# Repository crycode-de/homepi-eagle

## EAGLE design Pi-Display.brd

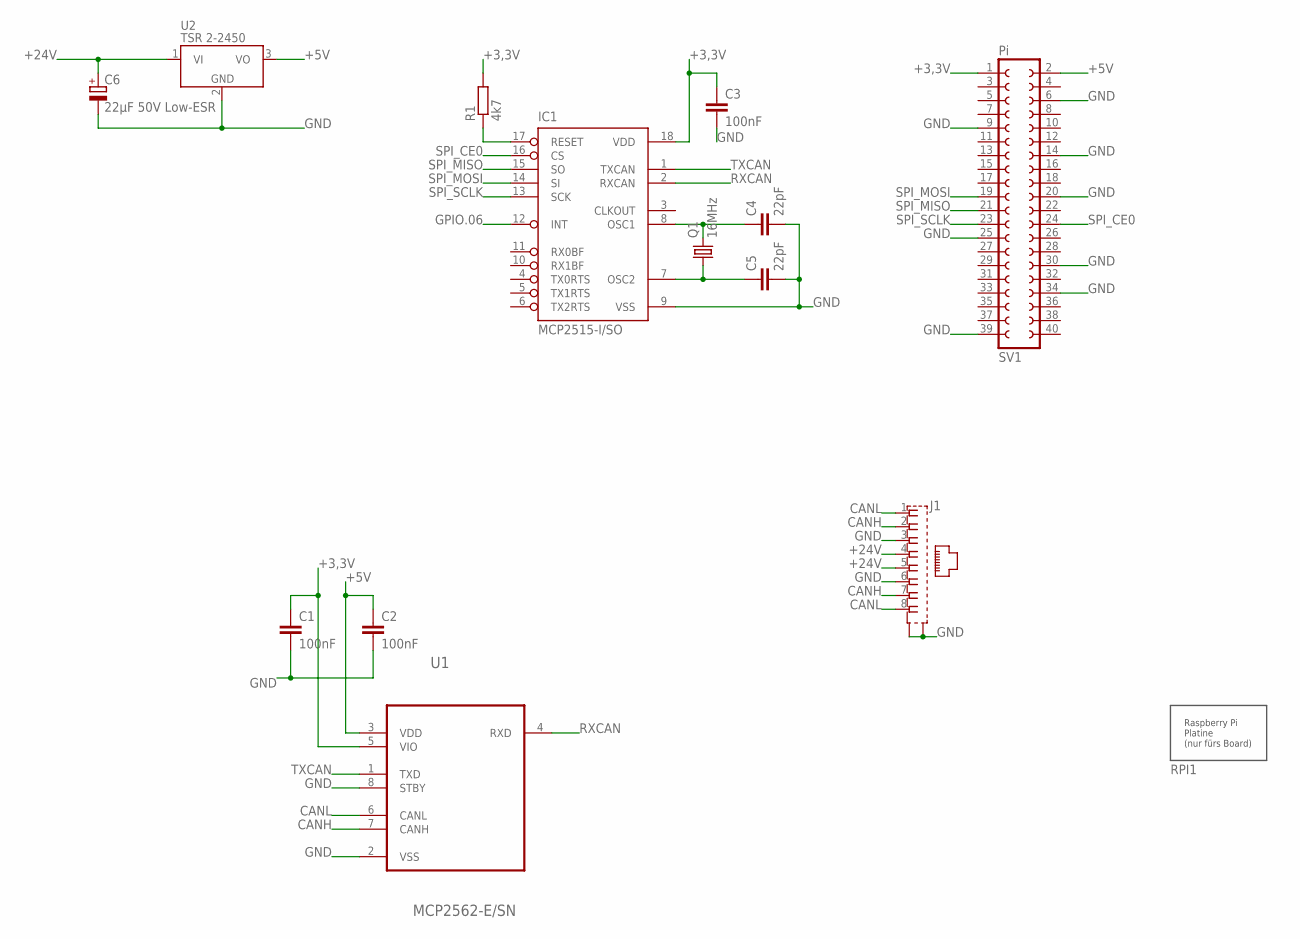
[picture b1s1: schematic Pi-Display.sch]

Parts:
C1, C2, C3: 100nF; C1206
C4, C5: 22pF; C1206
C6: 22µF 50V Low-ESR; E2-5
IC1: MCP2515-I/SO; SO18L
J1: 555141-1; MEBP_8-8G
Q1: 16MHz; HC49UP
R1: 4k7; R1206
RPI1: RASPBERRYPI-PLATINE
SV1: Pi; FE20-2
U1: MCP2562-E/SN; SO08
U2: TSR 2-2450; TSR-1

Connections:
+3,3V: C1.1, C3.1, IC1.18 (VDD), R1.2, SV1.1, U1.5 (VIO)
+5V: C2.1, SV1.2, U1.3 (VDD), U2.3 (VO)
+24V: C6.+, J1.4, J1.5, U2.1 (VI)
CANH: J1.2, J1.7, U1.7 (CANH)
CANL: J1.1, J1.8, U1.6 (CANL)
GND: C1.2, C2.2, C3.2, C4.2, C5.2, C6.-, IC1.9 (VSS), J1.3, J1.6, J1.G1 (S1), J1.G2 (S2), SV1.6, SV1.9, SV1.14, SV1.20, SV1.25, SV1.30, SV1.34, SV1.39, U1.2 (VSS), U1.8 (STBY), U2.2 (GND)
GPIO.06: IC1.12 (INT)
unnamed: C4.1, IC1.8 (OSC1), Q1.2
unnamed: IC1.17 (RESET), R1.1
unnamed: C5.1, IC1.7 (OSC2), Q1.1
RXCAN: IC1.2 (RXCAN), U1.4 (RXD)
SPI_CE0: IC1.16 (CS), SV1.24
SPI_MISO: IC1.15 (SO), SV1.21
SPI_MOSI: IC1.14 (SI), SV1.19
SPI_SCLK: IC1.13 (SCK), SV1.23
TXCAN: IC1.1 (TXCAN), U1.1 (TXD)

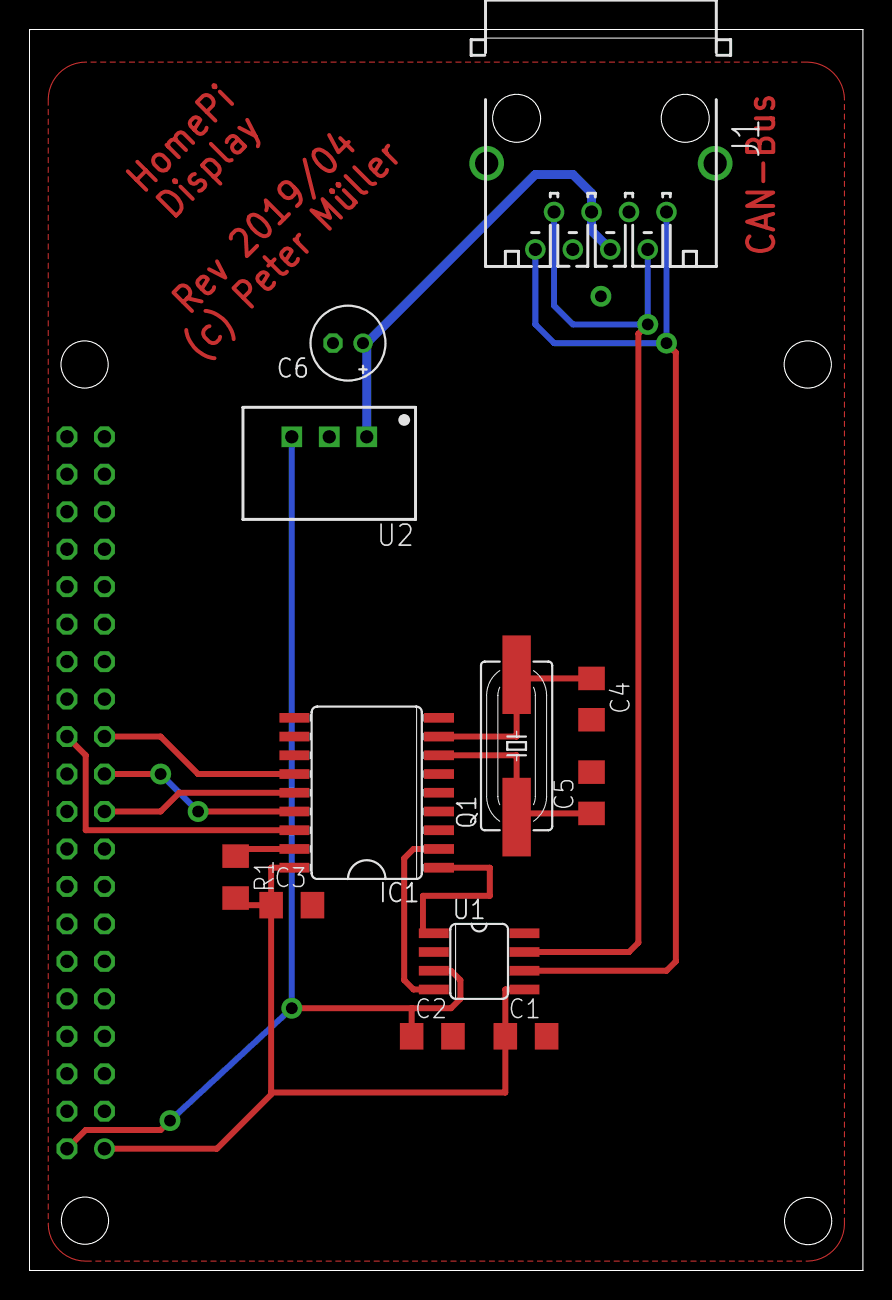
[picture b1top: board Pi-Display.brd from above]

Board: 2 copper layers, 56.5 x 84.1 mm, 14 parts (1 on the bottom side), 15 nets.

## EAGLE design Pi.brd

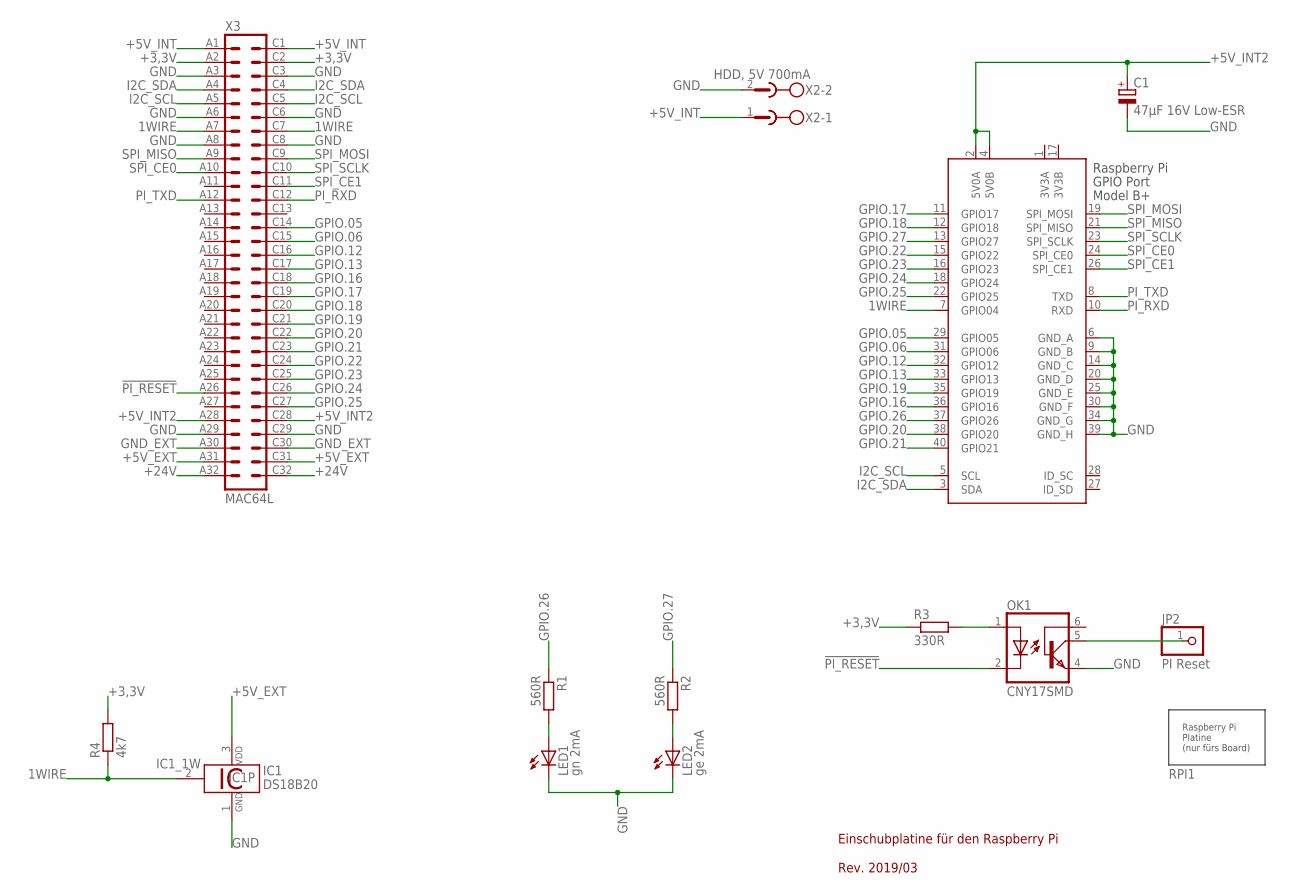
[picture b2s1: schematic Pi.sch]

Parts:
C1: 47µF 16V Low-ESR; E2-5
IC1: DS18B20; TO92-
JP2: PI Reset; 1X01
LED1: gn 2mA; LED3MM
LED2: ge 2mA; LED3MM
OK1: CNY17SMD; DIL06_SMD
R1, R2: 560R; R1206
R3: 330R; R1206
R4: 4k7; R1206
RPI1: RASPBERRYPI-PLATINE
X1: RASPI_GPIO_B+#_PIN; RASPI_GPIO_B+_PIN
X2: HDD, 5V 700mA; MSTBV2
X3: MAC64L

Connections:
1WIRE: IC1.2 (1W), R4.1, X1.7 (GPIO04), X3.A7, X3.C7
3V3A: X1.1 (3V3A)
3V3B: X1.17 (3V3B)
!PI_RESET: OK1.2 (C), X3.A26
+3,3V: R3.1, R4.2, X3.A2, X3.C2
+5V_EXT: IC1.3 (VDD), X3.A31, X3.C31
+5V_INT: X2.1, X3.A1, X3.C1
+5V_INT2: C1.+, X1.2 (5V0A), X1.4 (5V0B), X3.A28, X3.C28
+24V: X3.A32, X3.C32
GND: C1.-, IC1.1 (GND), LED1.K (C), LED2.K (C), OK1.4 (EMI), X1.6 (GND_A), X1.9 (GND_B), X1.14 (GND_C), X1.20 (GND_D), X1.25 (GND_E), X1.30 (GND_F), X1.34 (GND_G), X1.39 (GND_H), X2.2, X3.A3, X3.A6, X3.A8, X3.A29, X3.C3, X3.C6, X3.C8, X3.C29
GND_EXT: X3.A30, X3.C30
GPIO.05: X1.29 (GPIO05), X3.C14
GPIO.06: X1.31 (GPIO06), X3.C15
GPIO.12: X1.32 (GPIO12), X3.C16
GPIO.13: X1.33 (GPIO13), X3.C17
GPIO.16: X1.36 (GPIO16), X3.C18
GPIO.17: X1.11 (GPIO17), X3.C19
GPIO.18: X1.12 (GPIO18), X3.C20
GPIO.19: X1.35 (GPIO19), X3.C21
GPIO.20: X1.38 (GPIO20), X3.C22
GPIO.21: X1.40 (GPIO21), X3.C23
GPIO.22: X1.15 (GPIO22), X3.C24
GPIO.23: X1.16 (GPIO23), X3.C25
GPIO.24: X1.18 (GPIO24), X3.C26
GPIO.25: X1.22 (GPIO25), X3.C27
GPIO.26: R1.1, X1.37 (GPIO26)
GPIO.27: R2.1, X1.13 (GPIO27)
I2C_SCL: X1.5 (SCL), X3.A5, X3.C5
I2C_SDA: X1.3 (SDA), X3.A4, X3.C4
unnamed: LED2.A, R2.2
unnamed: OK1.1 (A), R3.2
unnamed: JP2.1, OK1.5 (COL)
unnamed: LED1.A, R1.2
PI_RXD: X1.10 (RXD), X3.C12
PI_TXD: X1.8 (TXD), X3.A12
SPI_CE0: X1.24 (SPI_CE0), X3.A10
SPI_CE1: X1.26 (SPI_CE1), X3.C11
SPI_MISO: X1.21 (SPI_MISO), X3.A9
SPI_MOSI: X1.19 (SPI_MOSI), X3.C9
SPI_SCLK: X1.23 (SPI_SCLK), X3.C10

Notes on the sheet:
Einschubplatine für den Raspberry Pi Rev. 2019/03

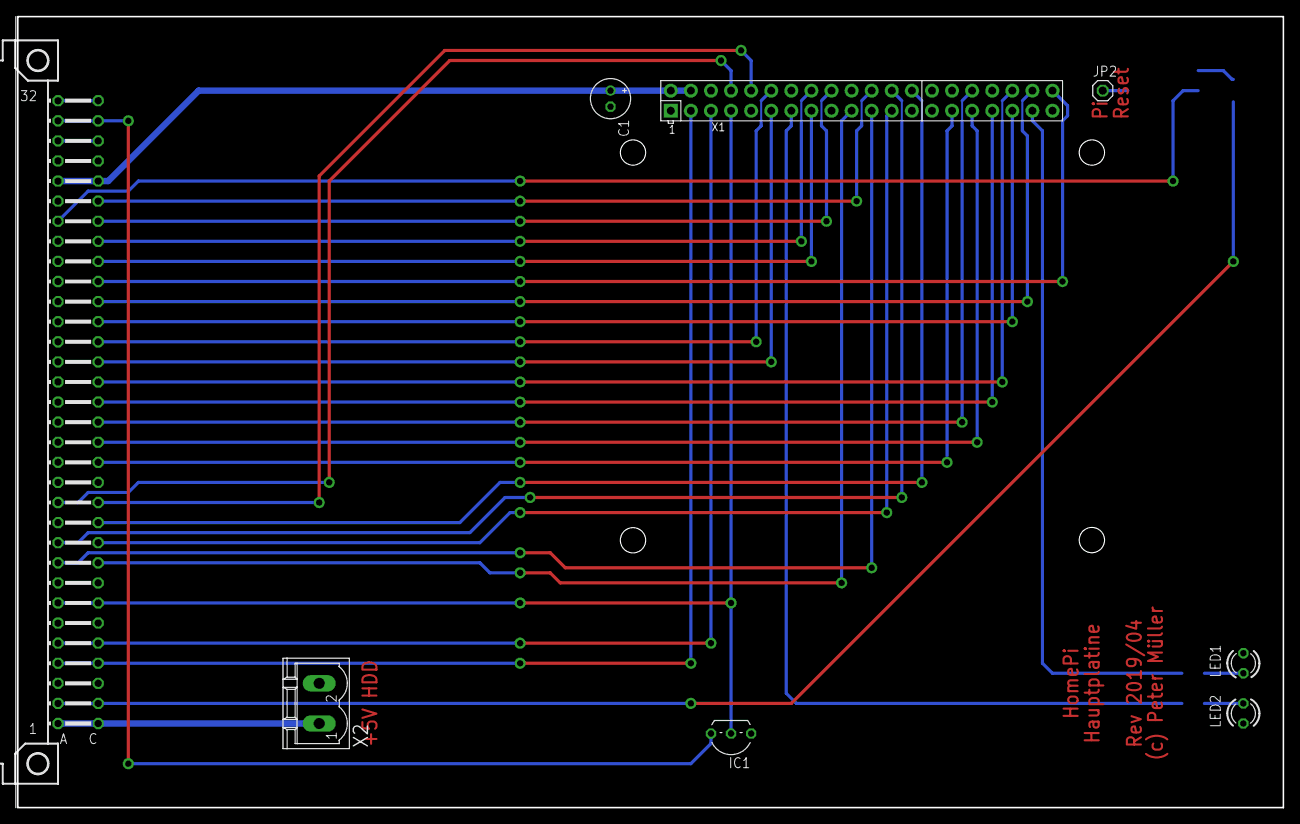
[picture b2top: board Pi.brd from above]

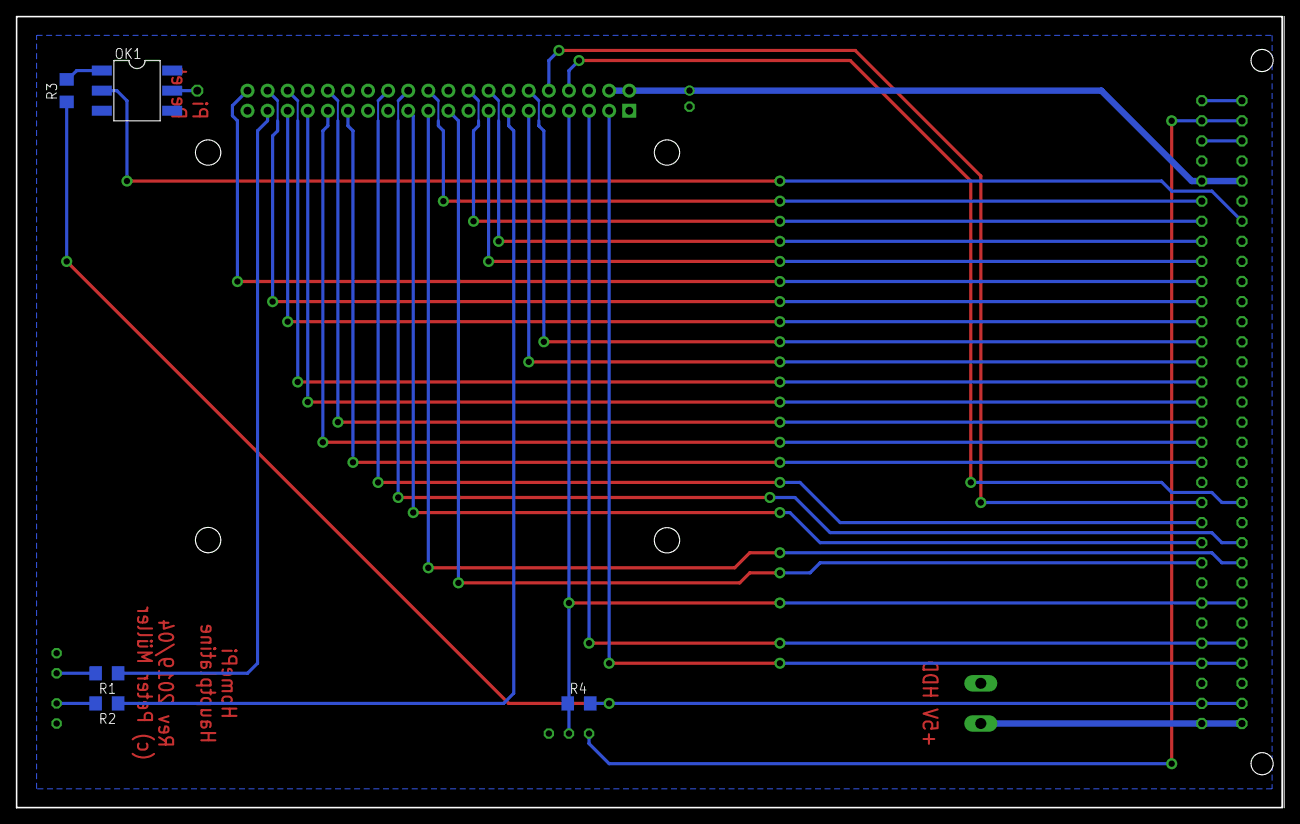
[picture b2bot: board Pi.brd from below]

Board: 2 copper layers, 160.0 x 100.0 mm, 14 parts (5 on the bottom side), 38 nets.

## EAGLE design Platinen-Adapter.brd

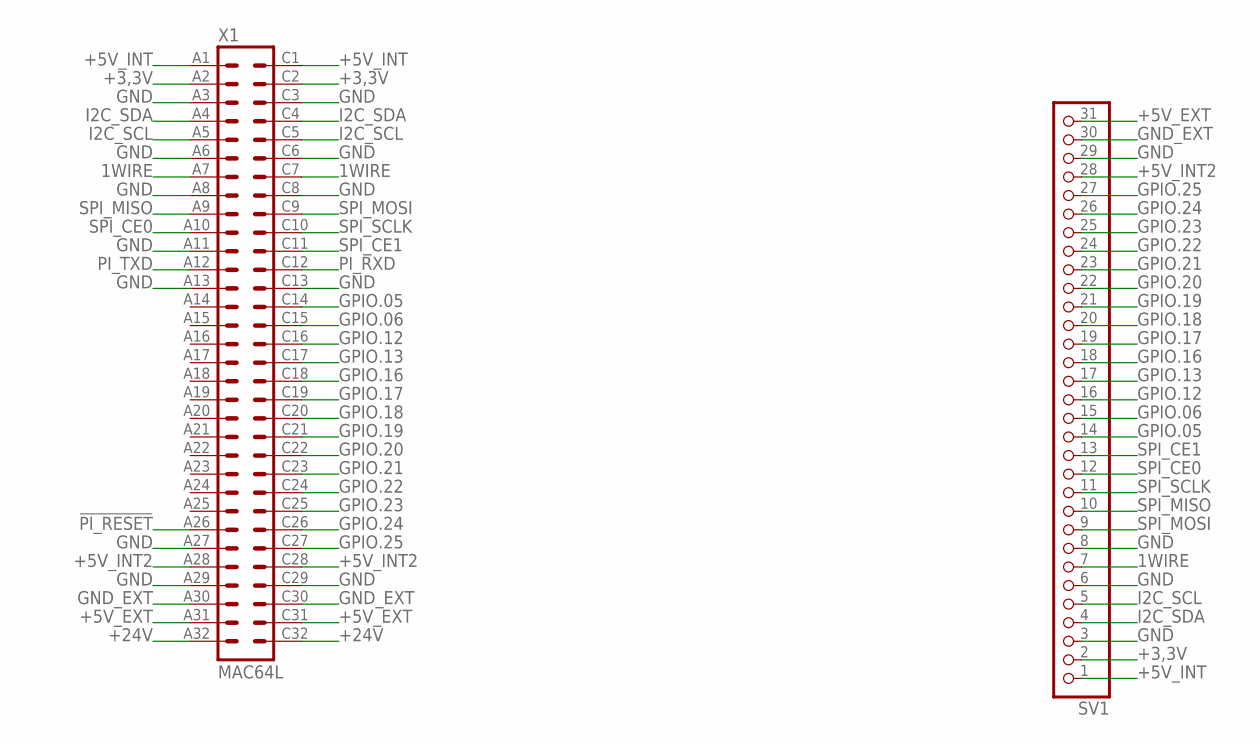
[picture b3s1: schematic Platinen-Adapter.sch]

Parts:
SV1: PINHD-1X31; 1X31
X1: MAC64L

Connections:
1WIRE: SV1.7, X1.A7, X1.C7
!PI_RESET: X1.A26
+3,3V: SV1.2, X1.A2, X1.C2
+5V_EXT: SV1.31, X1.A31, X1.C31
+5V_INT: SV1.1, X1.A1, X1.C1
+5V_INT2: SV1.28, X1.A28, X1.C28
+24V: X1.A32, X1.C32
GND: SV1.3, SV1.6, SV1.8, SV1.29, X1.A3, X1.A6, X1.A8, X1.A11, X1.A13, X1.A27, X1.A29, X1.C3, X1.C6, X1.C8, X1.C13, X1.C29
GND_EXT: SV1.30, X1.A30, X1.C30
GPIO.05: SV1.14, X1.C14
GPIO.06: SV1.15, X1.C15
GPIO.12: SV1.16, X1.C16
GPIO.13: SV1.17, X1.C17
GPIO.16: SV1.18, X1.C18
GPIO.17: SV1.19, X1.C19
GPIO.18: SV1.20, X1.C20
GPIO.19: SV1.21, X1.C21
GPIO.20: SV1.22, X1.C22
GPIO.21: SV1.23, X1.C23
GPIO.22: SV1.24, X1.C24
GPIO.23: SV1.25, X1.C25
GPIO.24: SV1.26, X1.C26
GPIO.25: SV1.27, X1.C27
I2C_SCL: SV1.5, X1.A5, X1.C5
I2C_SDA: SV1.4, X1.A4, X1.C4
PI_RXD: X1.C12
PI_TXD: X1.A12
SPI_CE0: SV1.12, X1.A10
SPI_CE1: SV1.13, X1.C11
SPI_MISO: SV1.10, X1.A9
SPI_MOSI: SV1.9, X1.C9
SPI_SCLK: SV1.11, X1.C10

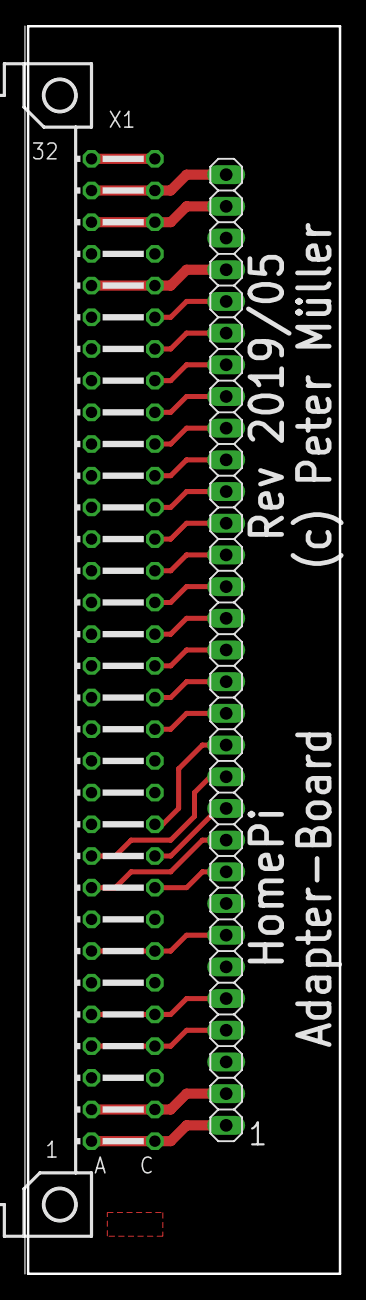
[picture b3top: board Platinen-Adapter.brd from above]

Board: 2 copper layers, 25.0 x 100.0 mm, 3 parts (1 on the bottom side), 29 nets.

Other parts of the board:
U$2: 30MM

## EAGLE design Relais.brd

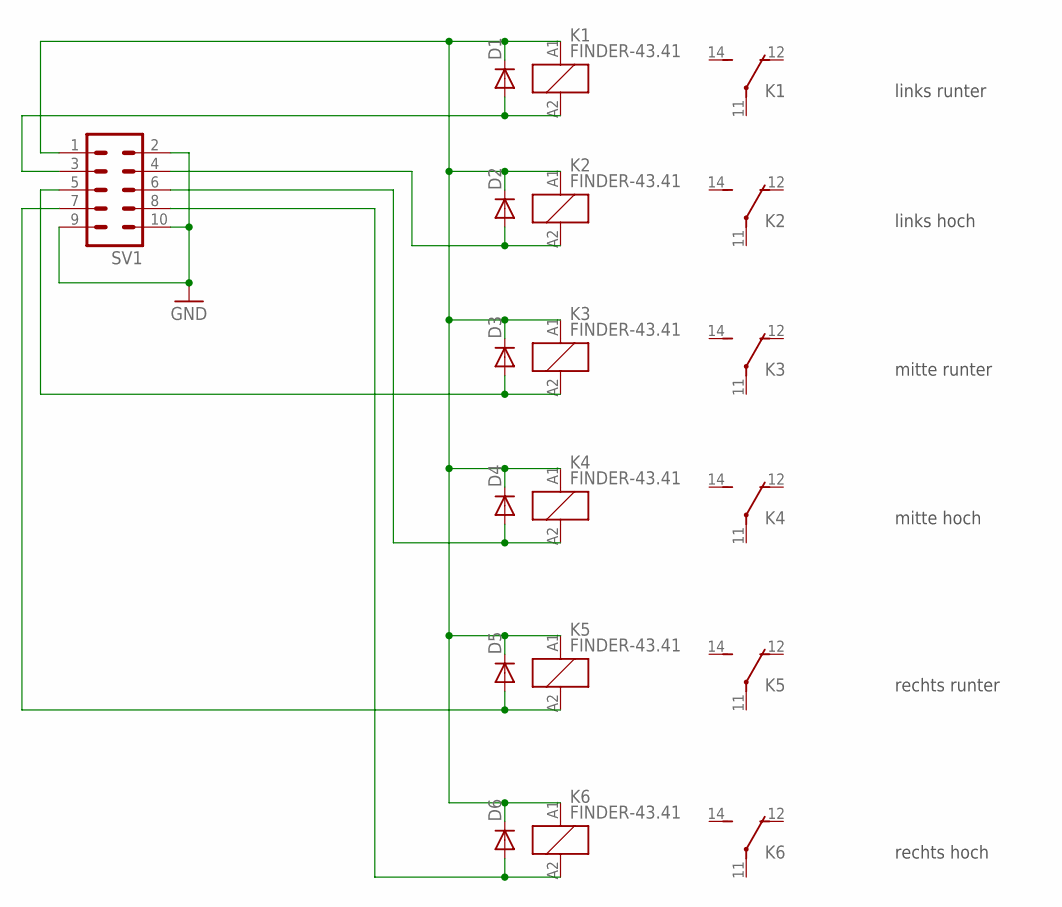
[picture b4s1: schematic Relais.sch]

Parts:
D1, D2, D3, D4, D5, D6: DIODE-D-7.5; D-7.5
K1, K2, K3, K4, K5, K6: FINDER-43.41
SV1: ML10

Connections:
GND: SV1.2, SV1.9, SV1.10
unnamed: D1.A, K1.A2 (2), SV1.3
unnamed: D2.A, K2.A2 (2), SV1.4
unnamed: D3.A, K3.A2 (2), SV1.5
unnamed: D4.A, K4.A2 (2), SV1.6
unnamed: D5.A, K5.A2 (2), SV1.7
unnamed: D6.A, K6.A2 (2), SV1.8
VCC: D1.C, D2.C, D3.C, D4.C, D5.C, D6.C, K1.A1 (1), K2.A1 (1), K3.A1 (1), K4.A1 (1), K5.A1 (1), K6.A1 (1), SV1.1

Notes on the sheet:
links runter
links hoch
mitte runter
mitte hoch
rechts runter
rechts hoch

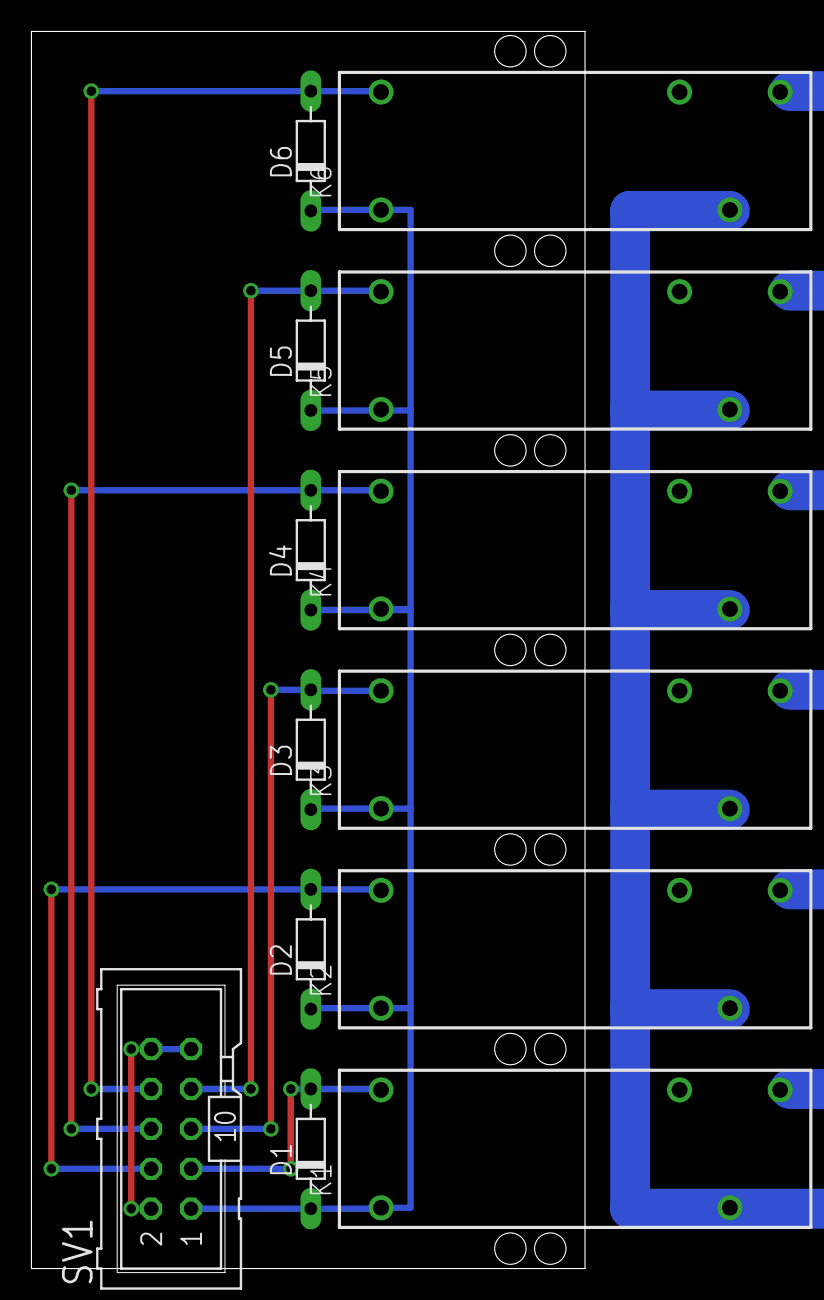
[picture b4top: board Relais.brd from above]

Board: 2 copper layers, 35.2 x 78.7 mm, 13 parts (0 on the bottom side), 8 nets.

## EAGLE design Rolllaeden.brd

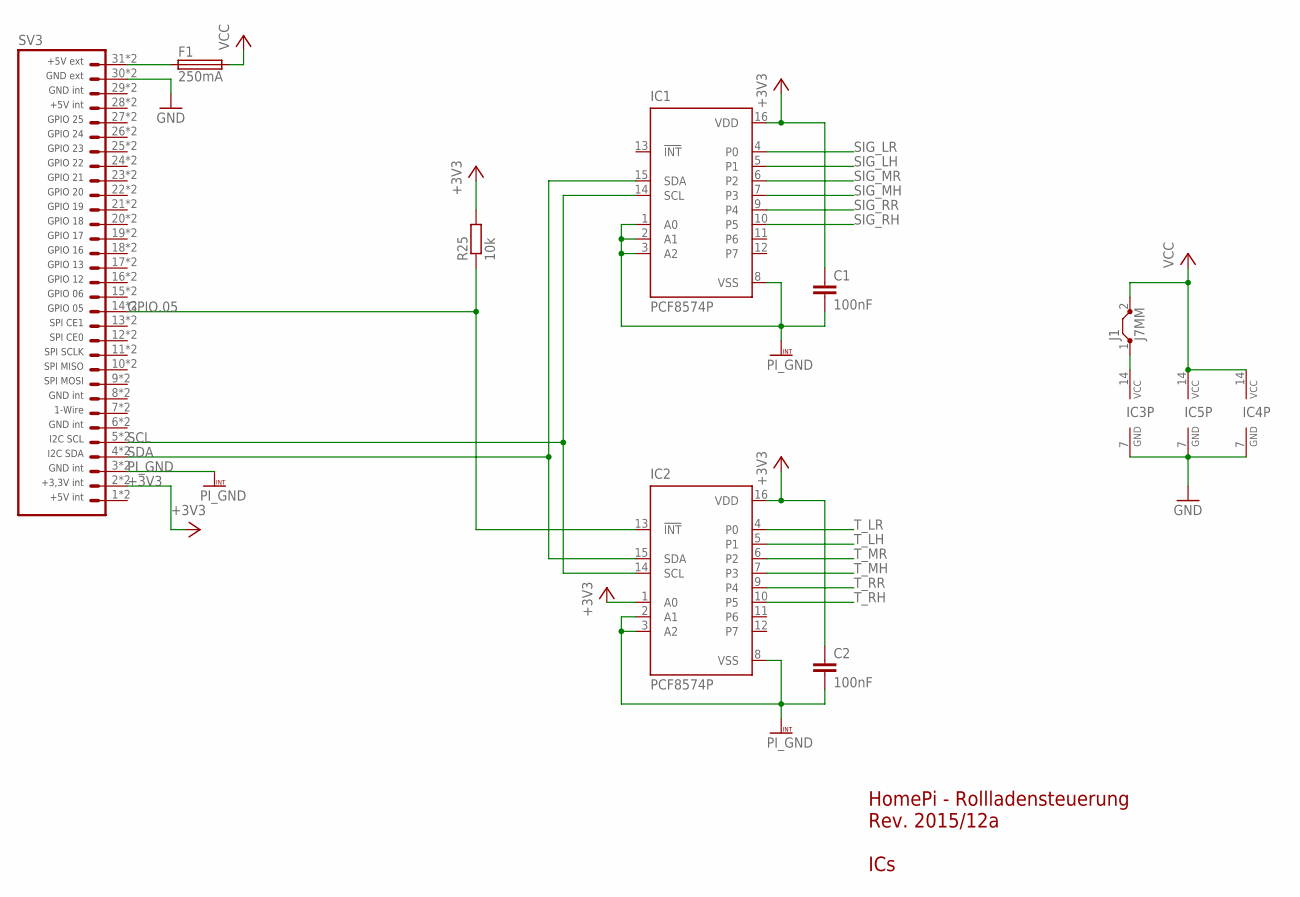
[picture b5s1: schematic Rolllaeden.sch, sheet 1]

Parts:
C1, C2: 100nF; C025-025X050
F1: 250mA; LITTLEFUSE
IC1, IC2: PCF8574P; DIL16
IC3: 74HCT04N; DIL14
IC4, IC5: 74HCT08N; DIL14
J1: J7MM; 07
R25: 10k; 0204V
SV3: PLATINENVERBINDER-31SMD; PLATINENVERBINDER-31-SMD

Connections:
+3V3: C1.1, C2.1, IC1.16 (VDD), IC2.1 (A0), IC2.16 (VDD), R25.2, SV3.2, SV3.2T (2); also elsewhere on the board
GND: IC3.7 (GND), IC4.7 (GND), IC5.7 (GND), SV3.30, SV3.30T (30); also elsewhere on the board
GPIO.05: IC2.13 (!INT), R25.1, SV3.14, SV3.14T (14)
unnamed: IC3.14 (VCC), J1.1
unnamed: F1.1, SV3.31, SV3.31T (31)
PI_GND: C1.2, C2.2, IC1.1 (A0), IC1.2 (A1), IC1.3 (A2), IC1.8 (VSS), IC2.2 (A1), IC2.3 (A2), IC2.8 (VSS), SV3.3, SV3.3T (3); also elsewhere on the board
SCL: IC1.14 (SCL), IC2.14 (SCL), SV3.5, SV3.5T (5)
SDA: IC1.15 (SDA), IC2.15 (SDA), SV3.4, SV3.4T (4)
SIG_LH: IC1.5 (P1); also elsewhere on the board
SIG_LR: IC1.4 (P0); also elsewhere on the board
SIG_MH: IC1.7 (P3); also elsewhere on the board
SIG_MR: IC1.6 (P2); also elsewhere on the board
SIG_RH: IC1.10 (P5); also elsewhere on the board
SIG_RR: IC1.9 (P4); also elsewhere on the board
T_LH: IC2.5 (P1); also elsewhere on the board
T_LR: IC2.4 (P0); also elsewhere on the board
T_MH: IC2.7 (P3); also elsewhere on the board
T_MR: IC2.6 (P2); also elsewhere on the board
T_RH: IC2.10 (P5); also elsewhere on the board
T_RR: IC2.9 (P4); also elsewhere on the board
VCC: F1.2, IC4.14 (VCC), IC5.14 (VCC), J1.2; also elsewhere on the board

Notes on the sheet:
HomePi - Rollladensteuerung Rev. 2015/12a ICs

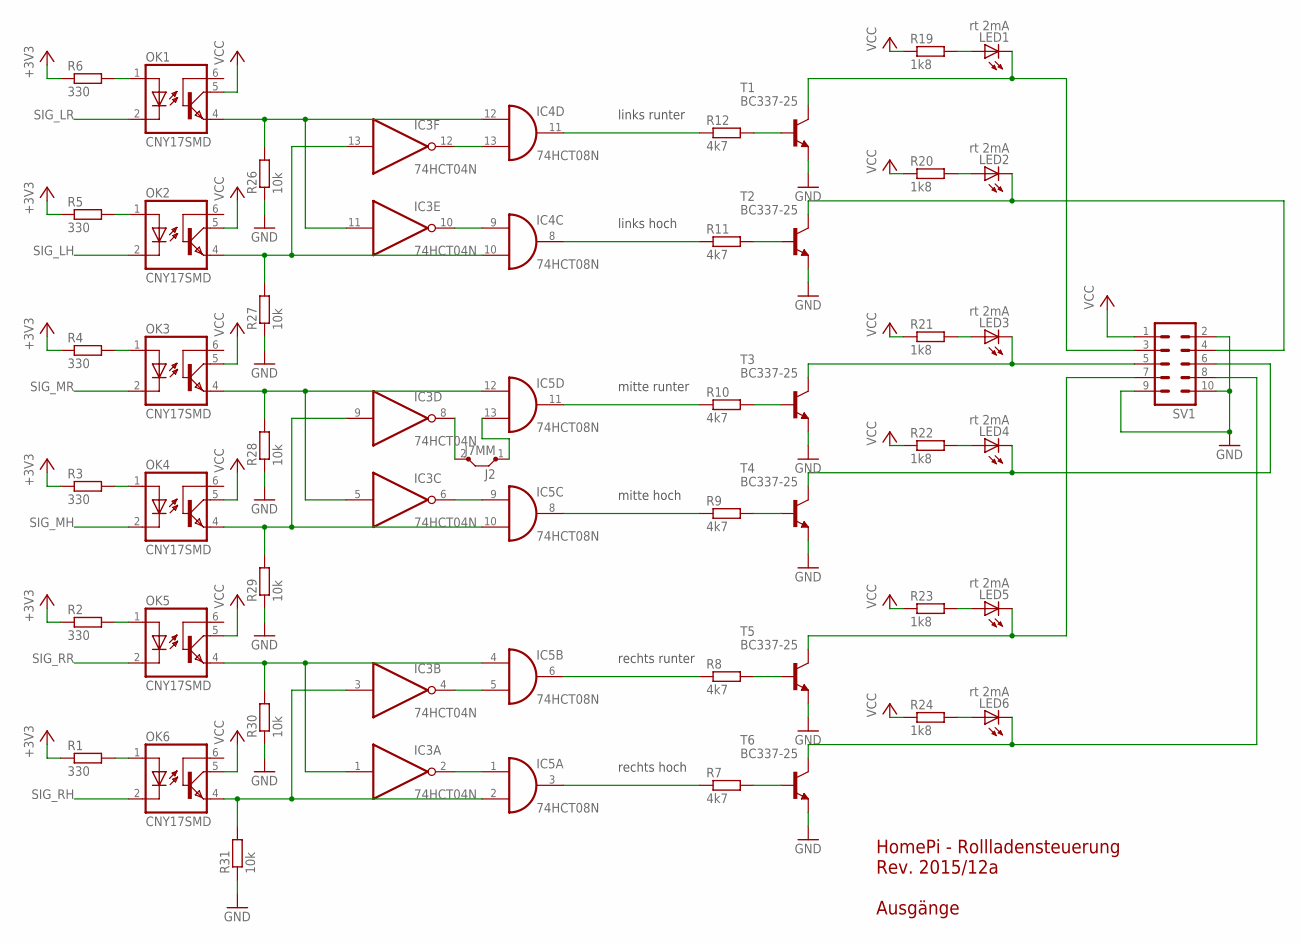
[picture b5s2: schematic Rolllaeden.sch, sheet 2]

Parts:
IC3: 74HCT04N; DIL14
IC4, IC5: 74HCT08N; DIL14
J2: J7MM; 07
LED1, LED2, LED3, LED4, LED5, LED6: rt 2mA; LED3MM
OK1, OK2, OK3, OK4, OK5, OK6: CNY17SMD; DIL06_SMD
R1, R2, R3, R4, R5, R6: 330; 0204V
R7, R8, R9, R10, R11, R12: 4k7; 0204V
R19, R20, R21, R22, R23, R24: 1k8; 0204V
R26, R27, R28, R29, R30, R31: 10k; 0204V
SV1: ML10
T1, T2, T3, T4, T5, T6: BC337-25; TO92-CBE

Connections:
+3V3: R1.1, R2.1, R3.1, R4.1, R5.1, R6.1; also elsewhere on the board
GND: R26.1, R27.1, R28.1, R29.1, R30.1, R31.1, SV1.2, SV1.9, SV1.10, T1.E, T2.E, T3.E, T4.E, T5.E, T6.E; also elsewhere on the board
unnamed: OK5.1 (A), R2.2
unnamed: OK6.1 (A), R1.2
unnamed: R9.2, T4.B
unnamed: IC3.3 (I), IC5.2 (I1), OK6.4 (EMI), R31.2
unnamed: IC5.3 (O), R7.1
unnamed: IC3.4 (O), IC5.5 (I1)
unnamed: R10.2, T3.B
unnamed: R8.2, T5.B
unnamed: IC3.2 (O), IC5.1 (I0)
unnamed: IC3.1 (I), IC5.4 (I0), OK5.4 (EMI), R30.2
unnamed: IC5.6 (O), R8.1
unnamed: OK2.1 (A), R5.2
unnamed: OK1.1 (A), R6.2
unnamed: LED1.A, R19.2
unnamed: OK4.1 (A), R3.2
unnamed: OK3.1 (A), R4.2
unnamed: IC3.9 (I), IC5.10 (I1), OK4.4 (EMI), R29.2
unnamed: IC3.5 (I), IC5.12 (I0), OK3.4 (EMI), R28.2
unnamed: IC3.8 (O), J2.2
unnamed: IC3.6 (O), IC5.9 (I0)
unnamed: R7.2, T6.B
unnamed: R11.2, T2.B
unnamed: R12.2, T1.B
unnamed: LED1.K (C), SV1.3, T1.C
unnamed: IC5.8 (O), R9.1
unnamed: IC5.11 (O), R10.1
unnamed: IC3.13 (I), IC4.10 (I1), OK2.4 (EMI), R27.2
unnamed: IC3.11 (I), IC4.12 (I0), OK1.4 (EMI), R26.2
unnamed: IC3.12 (O), IC4.13 (I1)
unnamed: IC3.10 (O), IC4.9 (I0)
unnamed: LED2.K (C), SV1.4, T2.C
unnamed: LED3.K (C), SV1.5, T3.C
unnamed: LED4.K (C), SV1.6, T4.C
unnamed: LED5.K (C), SV1.7, T5.C
unnamed: IC4.8 (O), R11.1
unnamed: IC4.11 (O), R12.1
unnamed: LED6.K (C), SV1.8, T6.C
unnamed: LED2.A, R20.2
unnamed: LED3.A, R21.2
unnamed: LED4.A, R22.2
unnamed: LED5.A, R23.2
unnamed: LED6.A, R24.2
unnamed: IC5.13 (I1), J2.1
SIG_LH: OK2.2 (C); also elsewhere on the board
SIG_LR: OK1.2 (C); also elsewhere on the board
SIG_MH: OK4.2 (C); also elsewhere on the board
SIG_MR: OK3.2 (C); also elsewhere on the board
SIG_RH: OK6.2 (C); also elsewhere on the board
SIG_RR: OK5.2 (C); also elsewhere on the board
VCC: OK1.5 (COL), OK2.5 (COL), OK3.5 (COL), OK4.5 (COL), OK5.5 (COL), OK6.5 (COL), R19.1, R20.1, R21.1, R22.1, R23.1, R24.1, SV1.1; also elsewhere on the board

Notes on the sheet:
rechts hoch
rechts runter
mitte hoch
mitte runter
links hoch
links runter
HomePi - Rollladensteuerung Rev. 2015/12a Ausgänge

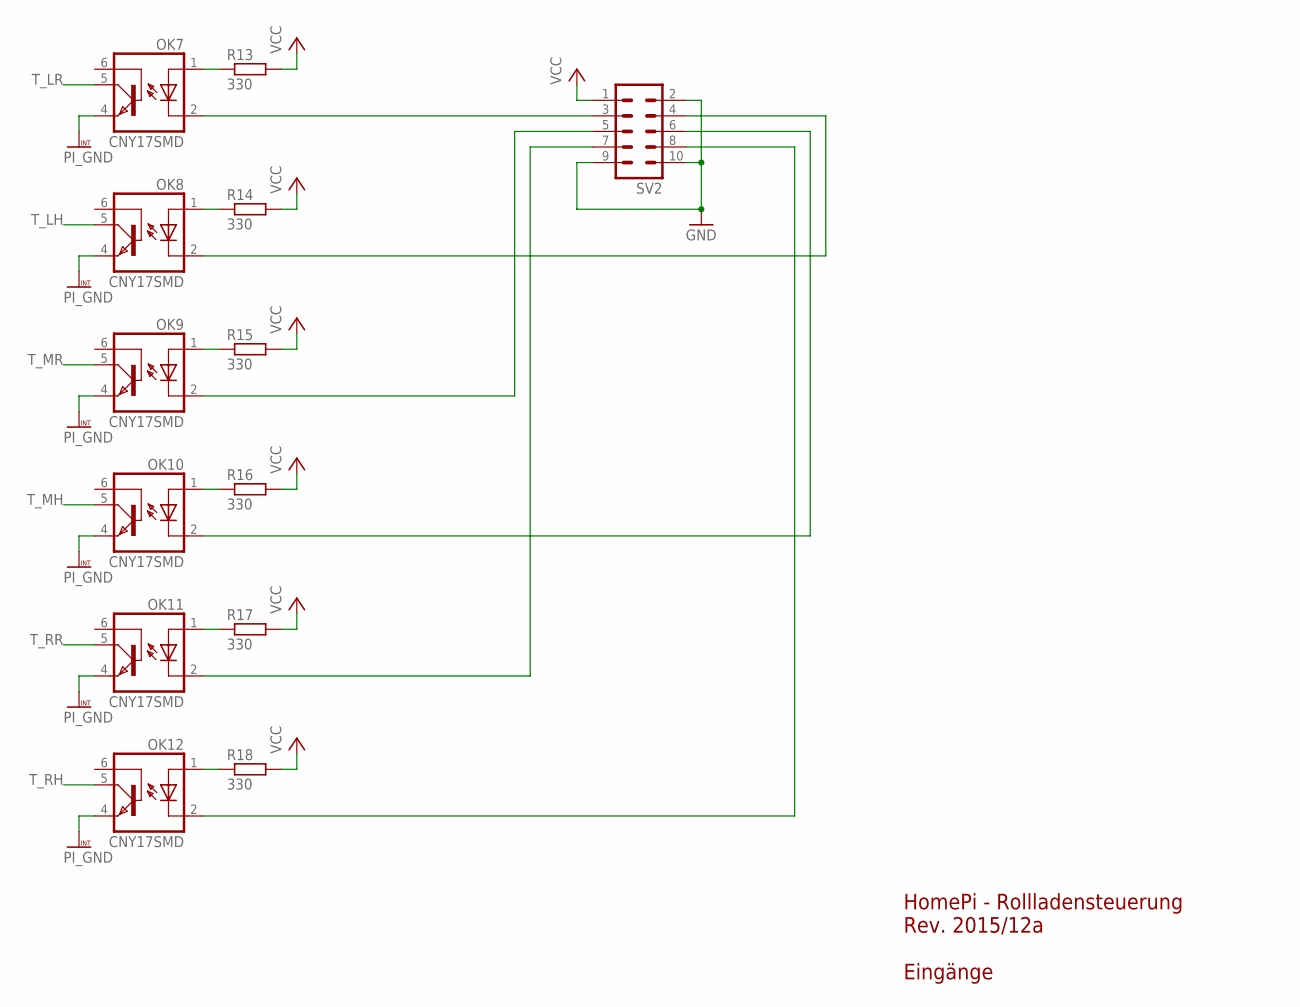
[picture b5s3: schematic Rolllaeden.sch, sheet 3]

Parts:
OK7, OK8, OK9, OK10, OK11, OK12: CNY17SMD; DIL06_SMD
R13, R14, R15, R16, R17, R18: 330; 0204V
SV2: ML10

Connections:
GND: SV2.2, SV2.9, SV2.10; also elsewhere on the board
unnamed: OK8.2 (C), SV2.4
unnamed: OK7.1 (A), R13.1
unnamed: OK8.1 (A), R14.1
unnamed: OK7.2 (C), SV2.3
unnamed: OK9.2 (C), SV2.5
unnamed: OK9.1 (A), R15.1
unnamed: OK10.1 (A), R16.1
unnamed: OK10.2 (C), SV2.6
unnamed: OK11.2 (C), SV2.7
unnamed: OK11.1 (A), R17.1
unnamed: OK12.1 (A), R18.1
unnamed: OK12.2 (C), SV2.8
PI_GND: OK7.4 (EMI), OK8.4 (EMI), OK9.4 (EMI), OK10.4 (EMI), OK11.4 (EMI), OK12.4 (EMI); also elsewhere on the board
T_LH: OK8.5 (COL); also elsewhere on the board
T_LR: OK7.5 (COL); also elsewhere on the board
T_MH: OK10.5 (COL); also elsewhere on the board
T_MR: OK9.5 (COL); also elsewhere on the board
T_RH: OK12.5 (COL); also elsewhere on the board
T_RR: OK11.5 (COL); also elsewhere on the board
VCC: R13.2, R14.2, R15.2, R16.2, R17.2, R18.2, SV2.1; also elsewhere on the board

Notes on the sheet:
HomePi - Rollladensteuerung Rev. 2015/12a Eingänge

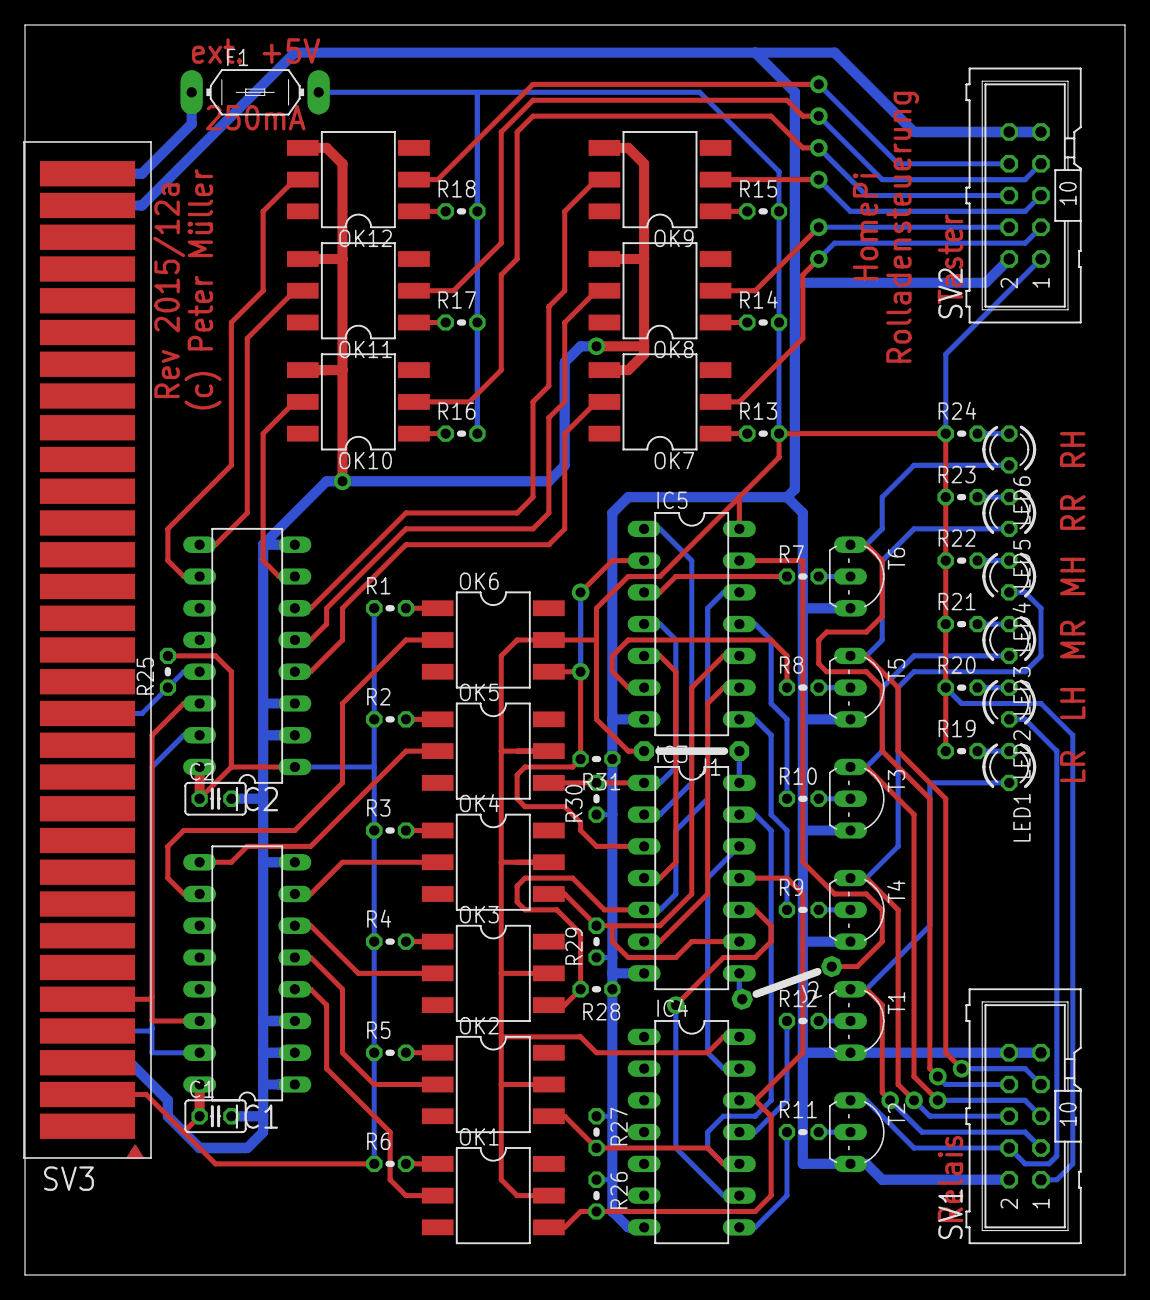
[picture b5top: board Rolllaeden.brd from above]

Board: 2 copper layers, 88.0 x 100.0 mm, 68 parts (0 on the bottom side), 76 nets.

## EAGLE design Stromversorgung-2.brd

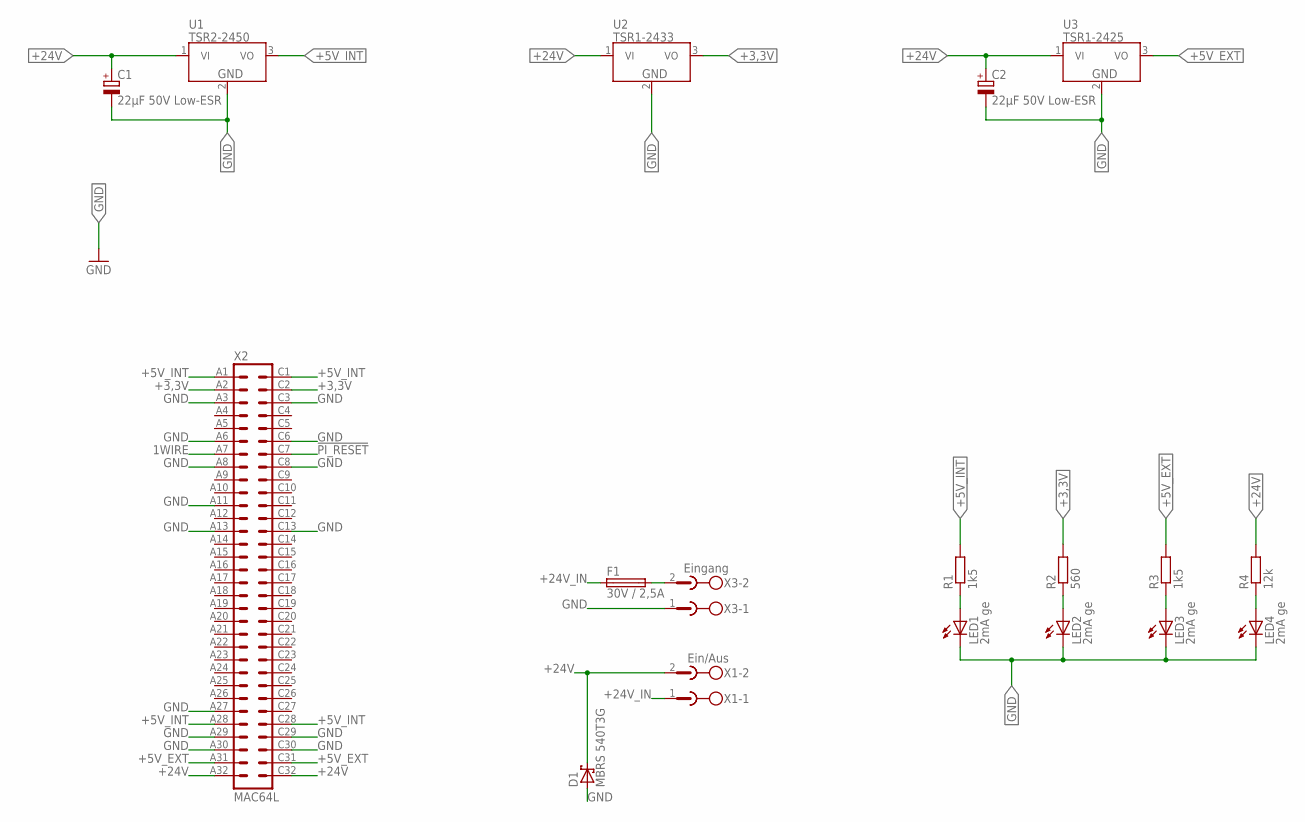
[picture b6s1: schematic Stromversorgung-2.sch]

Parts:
C1, C2: 22µF 50V Low-ESR; E2-5
D1: MBRS 540T3G; SMC
F1: 30V / 2,5A; LITTLEFUSE
LED1, LED2, LED3, LED4: 2mA ge; LED3MM
R1, R3: 1k5; R1206
R2: 560; R1206
R4: 12k; R1206
U1: TSR2-2450; TSR2
U2: TSR1-2433; TSR1
U3: TSR1-2425; TSR1
X1: Ein/Aus; MSTBA2
X2: MAC64L
X3: Eingang; MSTBA2

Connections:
1WIRE: X2.A7
!PI_RESET: X2.C7
+3,3V: R2.2, U2.3 (VO), X2.A2, X2.C2
+5V_EXT: R3.2, U3.3 (VO), X2.A31, X2.C31
+5V_INT: R1.2, U1.3 (VO), X2.A1, X2.A28, X2.C1, X2.C28
+24V: C1.+, C2.+, D1.C, R4.2, U1.1 (VI), U2.1 (VI), U3.1 (VI), X1.2, X2.A32, X2.C32
+24V_IN: F1.1, X1.1
+24V_IN_RAW: F1.2, X3.2
GND: C1.-, C2.-, D1.A, LED1.K (C), LED2.K (C), LED3.K (C), LED4.K (C), U1.2 (GND), U2.2 (GND), U3.2 (GND), X2.A3, X2.A6, X2.A8, X2.A11, X2.A13, X2.A27, X2.A29, X2.A30, X2.C3, X2.C6, X2.C8, X2.C13, X2.C29, X2.C30, X3.1
unnamed: LED4.A, R4.1
unnamed: LED1.A, R1.1
unnamed: LED2.A, R2.1
unnamed: LED3.A, R3.1
